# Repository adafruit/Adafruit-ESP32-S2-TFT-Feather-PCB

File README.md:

## Adafruit ESP32-S2 TFT Feather - 4MB Flash, 2MB PSRAM, STEMMA QT PCB

<a href="http://www.adafruit.com/products/5300"><br/>
Click here to purchase one from the Adafruit shop</a>

PCB files for the Adafruit ESP32-S2 TFT Feather - 4MB Flash, 2MB PSRAM, STEMMA QT. 

Format is EagleCAD schematic and board layout
* https://www.adafruit.com/product/5300

### Description

We've got a new machine here at Adafruit, it can uncover your deepest desires. Don't believe me? I'll turn it on right now to prove it to you! What, you want unlimited mozzarella sticks? OK well, that's not something we can provide. But we can provide your second-deepest desire: an ESP32-S2 Feather board with a built in IPS TFT color display. It's got all the gooeyness of a mozzarella stick features of a Feather main board, the comforting warmth of an ESP32-S2 WiFi microcontroller, and the crispness of a 240x135 pixel color TFT display. All that and it will even plug in nicely into a breadboard, terminal block wing, or Feather Doubler or even just stack on top of another wing.

This feather comes with native USB and 4 MB flash + 2 MB of PSRAM, so it is perfect for use with CircuitPython or Arduino with low-cost WiFi. Native USB means it can act like a keyboard or a disk drive. WiFi means its awesome for IoT projects. And Feather means it works with the large community of Feather Wings for expandability.

The ESP32-S2 is a highly-integrated, low-power, 2.4 GHz Wi-Fi System-on-Chip (SoC) solution that now has built-in native USB as well as some other interesting new technologies like Time of Flight distance measurements. With its state-of-the-art power and RF performance, this SoC is an ideal choice for a wide variety of application scenarios relating to the Internet of Things (IoT), wearable electronics, and smart homes.

Please note the Feather ESP32-S2 has a single-core 240 MHz chip, so it won't be as fast as ESP32's with dual-core. Also, there is no Bluetooth support. However, we are super excited about the ESP32-S2's native USB which unlocks a lot of capabilities for advanced interfacing! This ESP32-S2 mini-module we are using on the Feather comes with 4 MB flash and 2 MB PSRAM so you can buffer massive JSON files for parsing!

The color TFT is connected to the SPI pins, and uses additional pins for control that are not exposed to the breakout pads. It's the same display as you see here, with 240x135 pixels and is IPS so you get bright color at any angle. The backlight is also connected to a separate pin so you can PWM the backlight up and down as desired.

For low power usages, the Feather has a second AP2112 regulator. The regulator is controlled with a GPIO pin on the enable line and can shut off power to the Stemma QT port and TFT. There is also a separate power pin for the NeoPixel that can be used to disable it for even lower quiescent power. With everything off and in deep sleep mode, the TFT feather uses about 100uA of current.

### License

Adafruit invests time and resources providing this open source design, please support Adafruit and open-source hardware by purchasing products from [Adafruit](https://www.adafruit.com)!

Designed by Limor Fried/Ladyada for Adafruit Industries.

Creative Commons Attribution/Share-Alike, all text above must be included in any redistribution. 
See license.txt for additional details.

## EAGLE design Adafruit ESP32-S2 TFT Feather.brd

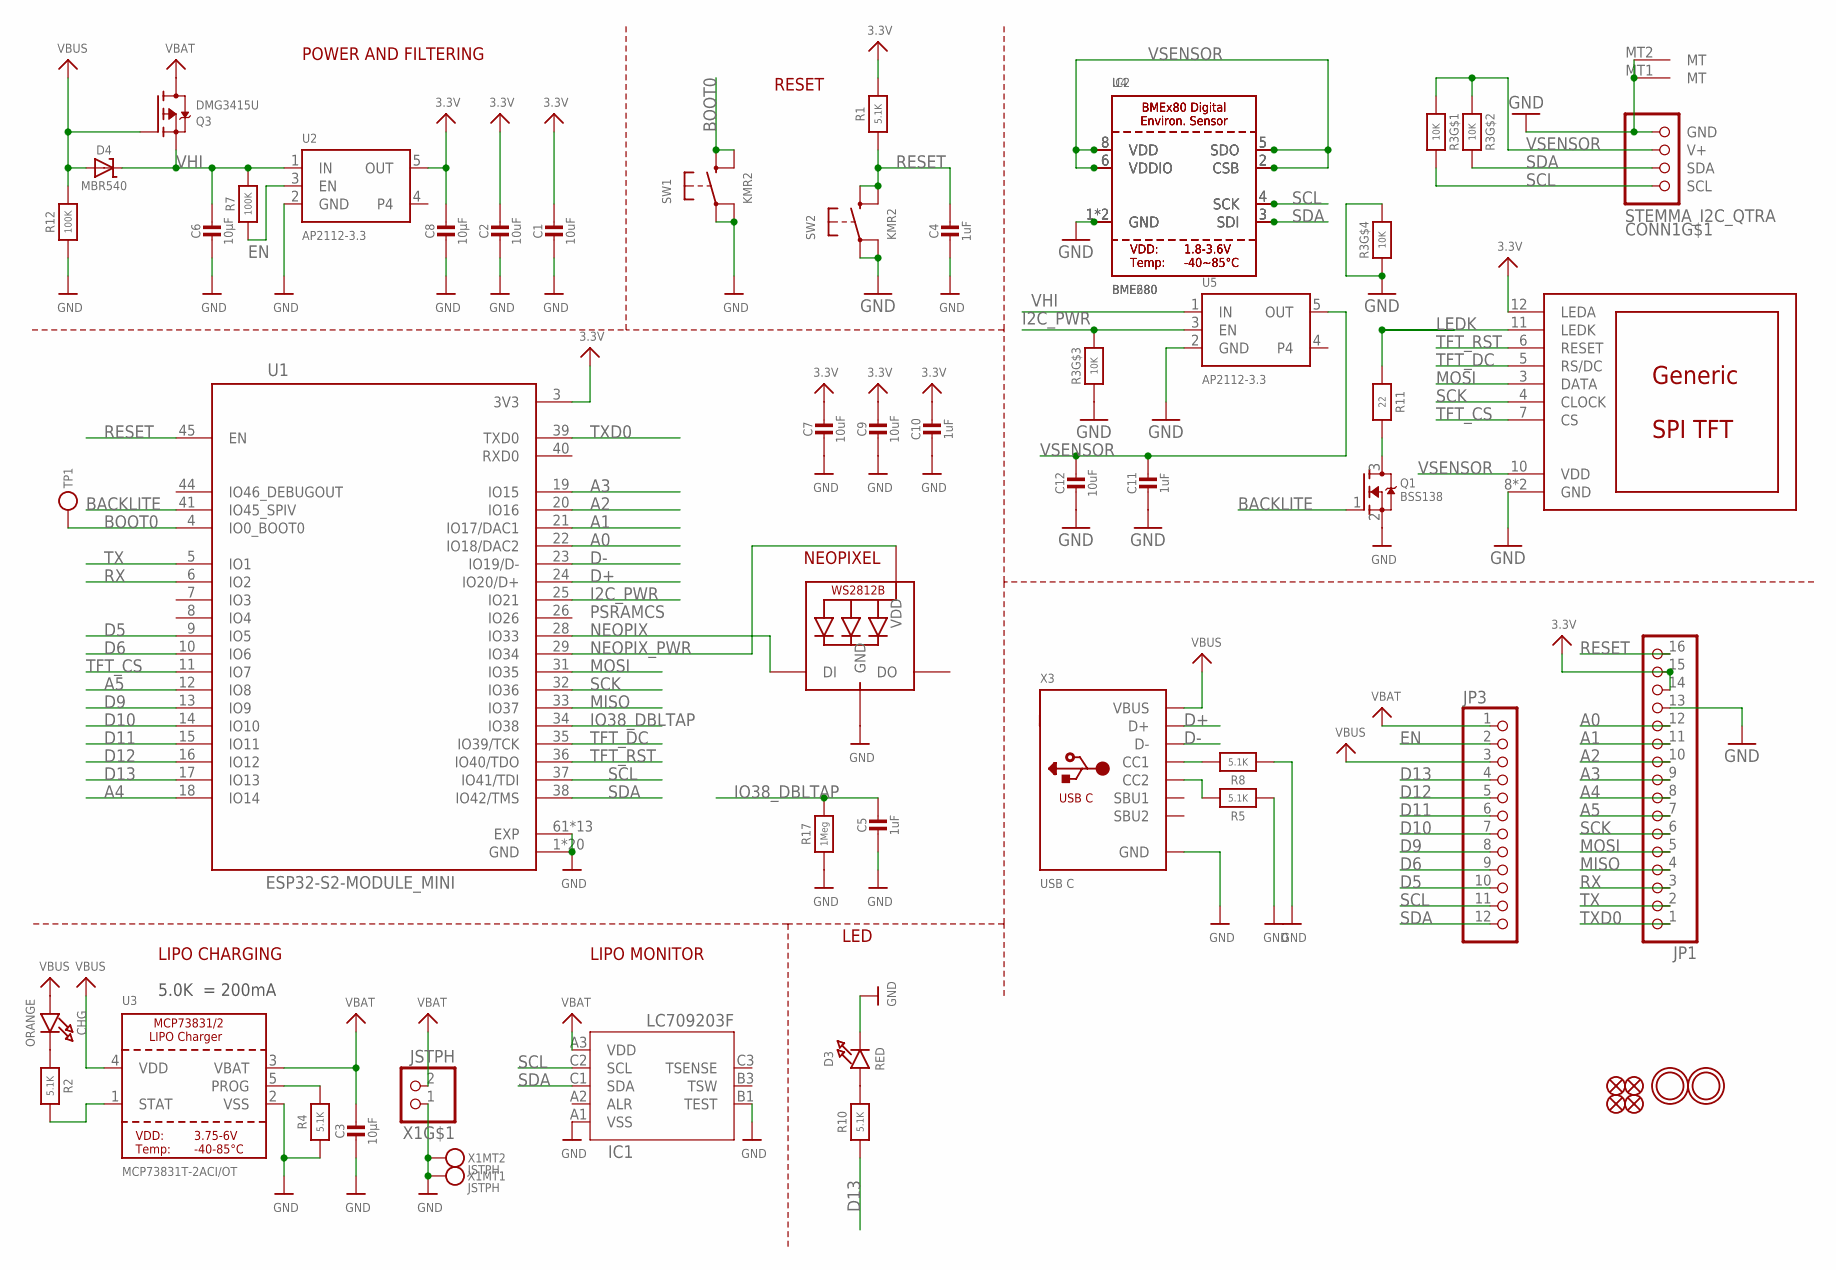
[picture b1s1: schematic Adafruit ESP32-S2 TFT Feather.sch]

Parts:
C1, C2, C7, C9, C12: 10uF; 0805-NO
C3, C6, C8: 10µF; 0805-NO
C4, C5, C10, C11: 1uF; 0603-NO
CHG: ORANGE; CHIPLED_0603_NOOUTLINE
CONN1: STEMMA_I2C_QTRA; JST_SH4_RA
D3: RED; CHIPLED_0603_NOOUTLINE
D4: MBR540; SOD-123
DISP1: DISP_LCD_GENERIC_SPI_1.14IN_240X135_WRAPUNDER; TFT_1.14IN_240X135_WRAPUNDER
IC1: LC709203F/MH; WLCSP9
IC2: BME680
JP1: HEADER-1X16_MIN; 1X16_ROUND_MIN
JP3: HEADER-1X12_MIN; 1X12_ROUND_MIN
LED1: WS2812B_SK6805_1515; SK6805_1515
Q1: BSS138; SOT23-R
Q3: DMG3415U; SOT23-R
R1, R2, R4, R5, R8, R10: 5.1K; 0603-NO
R3: 10K; RESPACK_4X0603
R7, R12: 100K; 0603-NO
R11: 22; 0603-NO
R17: 1Meg; 0603-NO
SW1, SW2: KMR2; BTN_KMR2_4.6X2.8
TP1: TESTPOINTROUND1.5MMNO; TESTPOINT_ROUND_1.5MM_NO
U1: ESP32-S2-MODULE_MINI; QFN60_ESP32-S2-MINI-1_EXP
U2, U5: AP2112-3.3; SOT23-5
U3: MCP73831T-2ACI/OT; SOT23-5
U4: BME280
U$31, U$32: MOUNTINGHOLE2.5; MOUNTINGHOLE_2.5_PLATED
U$34, U$35, U$55, U$56: FIDUCIAL_1MM
X1: JSTPH; JSTPH2_BATT
X3: USB C; USB_C_CUSB31-CFM2AX-01-X

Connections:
3.3V: C1.1, C2.1, C7.1, C8.1, C9.1, C10.1, DISP1.12 (LEDA), JP1.14, JP1.15, R1.2, U1.3 (3V3), U2.5 (OUT)
A0: JP1.12, U1.22 (IO18/DAC2)
A1: JP1.11, U1.21 (IO17/DAC1)
A2: JP1.10, U1.20 (IO16)
A3: JP1.9, U1.19 (IO15)
A4: JP1.8, U1.18 (IO14)
A5: JP1.7, U1.12 (IO8)
BACKLITE: Q1.1 (G), U1.41 (IO45_SPIV)
BOOT0: SW1.B (S), SW1.B' (S1), TP1.P$1, U1.4 (IO0_BOOT0)
D5: JP3.10, U1.9 (IO5)
D6: JP3.9, U1.10 (IO6)
D9: JP3.8, U1.13 (IO9)
D10: JP3.7, U1.14 (IO10)
D11: JP3.6, U1.15 (IO11)
D12: JP3.5, U1.16 (IO12)
D13: JP3.4, R10.1, U1.17 (IO13)
D+: U1.24 (IO20/D+), X3.A6 (D+), X3.B6 (D+)
D-: U1.23 (IO19/D-), X3.A7 (D-), X3.B7 (D-)
EN: JP3.2, R7.1, U2.3 (EN)
GND: C1.2, C2.2, C3.2, C4.2, C5.2, C6.2, C7.2, C8.2, C9.2, C10.2, C11.2, C12.2, CONN1.1 (GND), CONN1.MT1 (MT), CONN1.MT2 (MT), D3.C, DISP1.8 (GND), DISP1.13 (GND), IC1.A1 (VSS), IC1.B1 (TEST), IC2.1 (GND), IC2.7 (GND), JP1.13, LED1.4 (GND), Q1.2 (S), R3.3 (1), R3.4 (1), R3.5 (2), R4.1, R5.1, R8.1, R12.1, R17.1, SW1.A, SW1.A' (P1), SW2.A, SW2.A' (P1), U1.1 (GND), U1.2 (GND), U1.30 (GND), U1.42 (GND), U1.43 (GND), U1.46 (GND), U1.47 (GND), U1.48 (GND), U1.49 (GND), U1.50 (GND), U1.51 (GND), U1.52 (GND), U1.53 (GND), U1.54 (GND), U1.55 (GND), U1.56 (GND), U1.57 (GND), U1.58 (GND), U1.59 (GND), U1.60 (GND), U1.61 (EXP), U1.62 (EXP), U1.63 (EXP), U1.64 (EXP), U1.65 (EXP), U1.66 (EXP), U1.67 (EXP), U1.68 (EXP), U1.69 (EXP), U1.70 (EXP), U1.71 (EXP), U1.72 (EXP), U1.73 (EXP), U2.2 (GND), U3.2 (VSS), U4.1 (GND), U4.7 (GND), U5.2 (GND), X1.1, X1.NC1, X1.NC2, X3.A1B12 (GND), X3.B1A12 (GND)
I2C_PWR: R3.6 (2), U1.25 (IO21), U5.3 (EN)
IO38_DBLTAP: C5.1, R17.2, U1.34 (IO38)
LEDK: DISP1.11 (LEDK), R11.1
MISO: JP1.4, U1.33 (IO37)
MOSI: DISP1.3 (DATA), JP1.5, U1.31 (IO35)
unnamed: CHG.C, R2.1
unnamed: Q1.3 (D), R11.2
unnamed: R2.2, U3.1 (STAT)
unnamed: R4.2, U3.5 (PROG)
unnamed: D3.A, R10.2
unnamed: R8.2, X3.A5 (CC1)
unnamed: R5.2, X3.B5 (CC2)
NEOPIX: LED1.1 (DI), U1.28 (IO33)
NEOPIX_PWR: LED1.2 (VDD), U1.29 (IO34)
RESET: C4.1, JP1.16, R1.1, SW2.B (S), SW2.B' (S1), U1.45 (EN)
RX: JP1.3, U1.6 (IO2)
SCK: DISP1.4 (CLOCK), JP1.6, U1.32 (IO36)
SCL: CONN1.4 (SCL), IC1.C2 (SCL), IC2.4 (SCK), JP3.11, R3.8 (2), U1.37 (IO41/TDI), U4.4 (SCK)
SDA: CONN1.3 (SDA), IC1.C1 (SDA), IC2.3 (SDI), JP3.12, R3.7 (2), U1.38 (IO42/TMS), U4.3 (SDI)
TFT_CS: DISP1.7 (CS), U1.11 (IO7)
TFT_DC: DISP1.5 (RS/DC), U1.35 (IO39/TCK)
TFT_RST: DISP1.6 (RESET), U1.36 (IO40/TDO)
TX: JP1.2, U1.5 (IO1)
TXD0: JP1.1, U1.39 (TXD0)
VBAT: C3.1, IC1.A3 (VDD), JP3.1, Q3.3 (D), U3.3 (VBAT), X1.2
VBUS: CHG.A, D4.A, JP3.3, Q3.1 (G), R12.2, U3.4 (VDD), X3.A4B9 (VBUS), X3.B4A9 (VBUS)
VHI: C6.1, D4.C, Q3.2 (S), R7.2, U2.1 (IN), U5.1 (IN)
VSENSOR: C11.1, C12.1, CONN1.2 (V+), DISP1.10 (VDD), IC2.2 (CSB), IC2.5 (SDO), IC2.6 (VDDIO), IC2.8 (VDD), R3.1, R3.2 (1), U4.2 (CSB), U4.5 (SDO), U4.6 (VDDIO), U4.8 (VDD), U5.5 (OUT)

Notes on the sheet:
POWER AND FILTERING
RESET
5.0K = 200mA
LIPO CHARGING
LED
PSRAMCS
NEOPIXEL
LIPO MONITOR

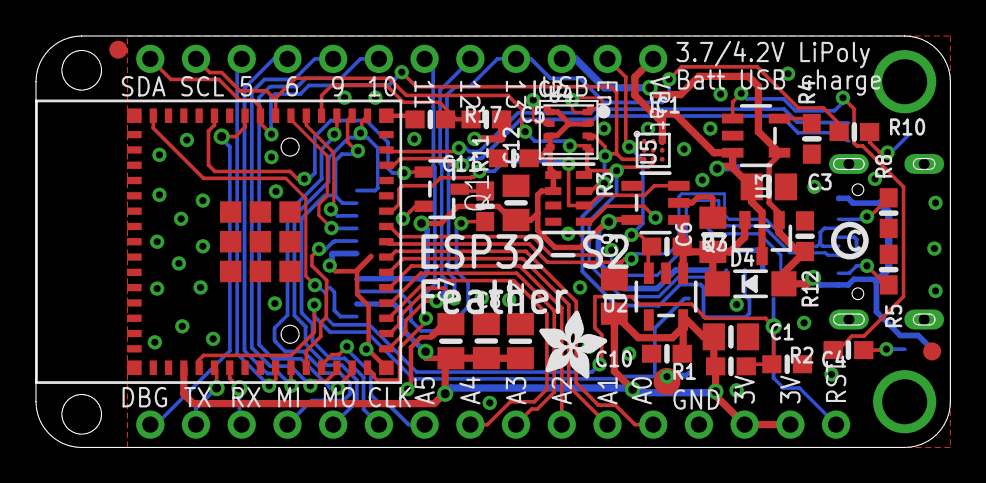
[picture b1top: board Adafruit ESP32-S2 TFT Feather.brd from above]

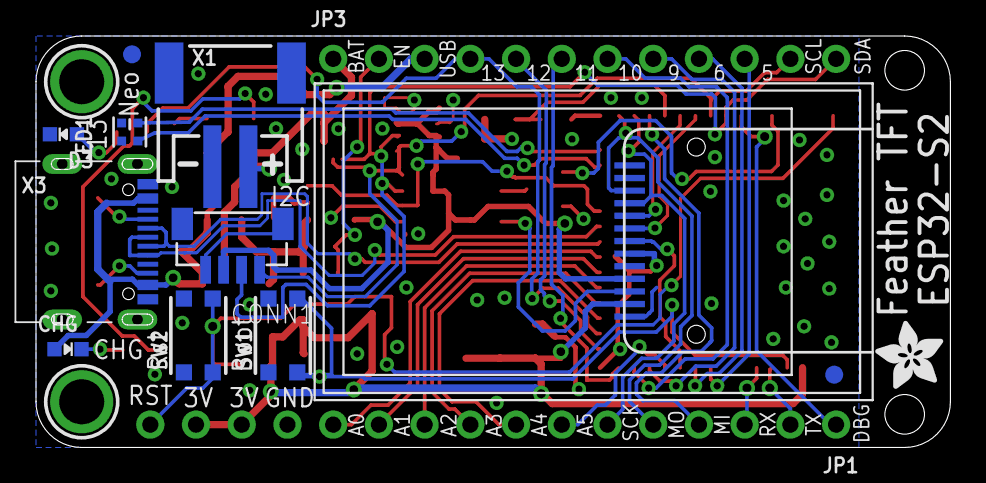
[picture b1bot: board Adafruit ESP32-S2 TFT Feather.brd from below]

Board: 2 copper layers, 50.8 x 22.9 mm, 54 parts (16 on the bottom side), 48 nets.

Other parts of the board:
U$7: PCBFEAT-REV-040
U$9, U$54: ADAFRUIT_3.5MM

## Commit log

2022-01-10 Add PrettyPins.
2022-01-12 Add factory reset and bootloader files.
2022-02-16 Updated pin name.
2023-06-22 Updating factory reset files
    Now checks for either LC or MAX battery monitor

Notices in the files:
parts and their libraries:
microbuilder: This work is placed in the public domain, and may be freely used for commercial and non-commercial work with the following conditions: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
